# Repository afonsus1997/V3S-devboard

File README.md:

# V3S-devboard

## Hardware

Using V3S lib from https://github.com/balmerdx/AllwinnerV3S_KiCad

## Software

Build environment based on Funkey project

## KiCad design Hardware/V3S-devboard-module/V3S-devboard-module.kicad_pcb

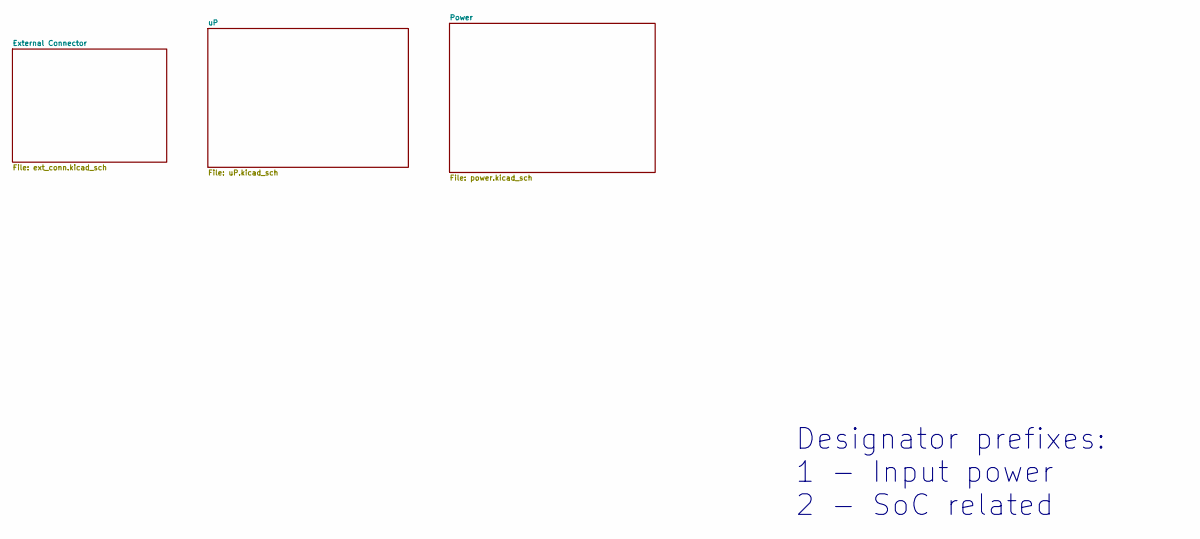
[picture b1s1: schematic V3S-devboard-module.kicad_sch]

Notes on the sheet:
Designator prefixes: 1 - Input power 2 - SoC related

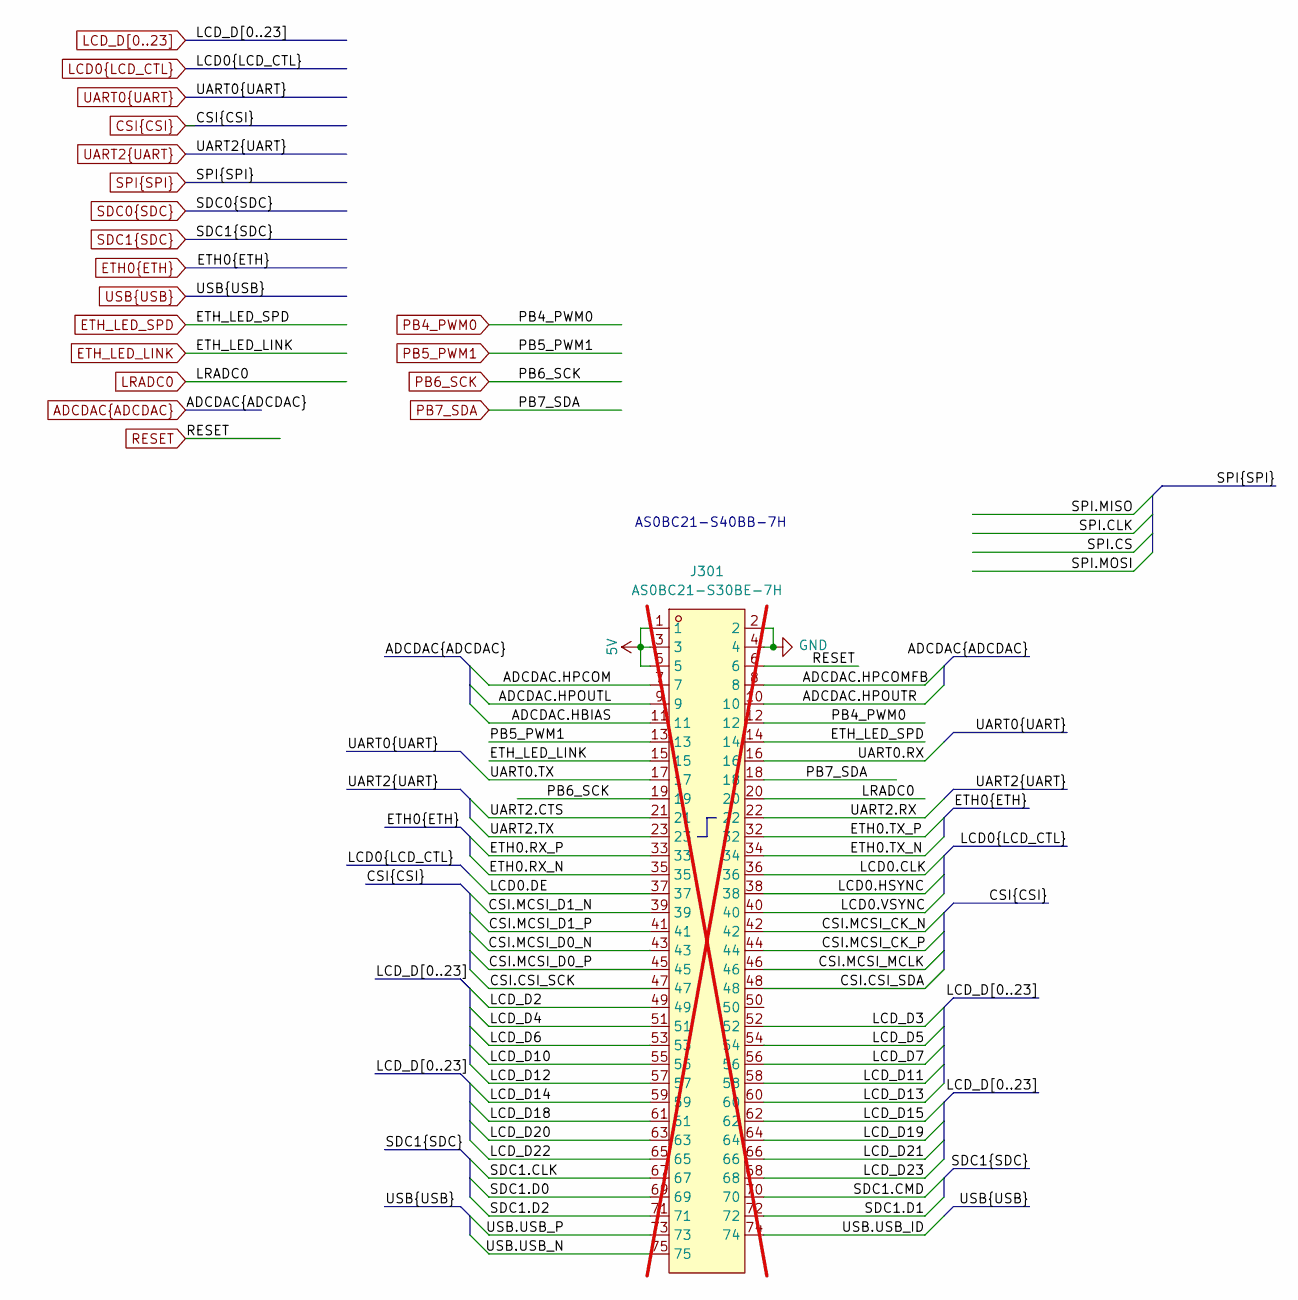
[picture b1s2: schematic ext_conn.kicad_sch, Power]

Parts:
J301: AS0BC21-S30BE-7H; m2-padKeyE; LCSC Part C3020019; not fitted

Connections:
5V: J301.1, J301.3, J301.5; also elsewhere on the board
ADCDAC.HBIAS: J301.11; also elsewhere on the board
ADCDAC.HPCOM: J301.7; also elsewhere on the board
ADCDAC.HPCOMFB: J301.8; also elsewhere on the board
ADCDAC.HPOUTL: J301.9; also elsewhere on the board
ADCDAC.HPOUTR: J301.10; also elsewhere on the board
CSI.CSI_SCK: J301.47; also elsewhere on the board
CSI.CSI_SDA: J301.48; also elsewhere on the board
CSI.MCSI_CK_N: J301.42; also elsewhere on the board
CSI.MCSI_CK_P: J301.44; also elsewhere on the board
CSI.MCSI_D0_N: J301.43; also elsewhere on the board
CSI.MCSI_D0_P: J301.45; also elsewhere on the board
CSI.MCSI_D1_N: J301.39; also elsewhere on the board
CSI.MCSI_D1_P: J301.41; also elsewhere on the board
CSI.MCSI_MCLK: J301.46; also elsewhere on the board
ETH0.RX_N: J301.35; also elsewhere on the board
ETH0.RX_P: J301.33; also elsewhere on the board
ETH0.TX_N: J301.34; also elsewhere on the board
ETH0.TX_P: J301.32; also elsewhere on the board
ETH_LED_LINK: J301.15; also elsewhere on the board
ETH_LED_SPD: J301.14; also elsewhere on the board
GND: J301.2, J301.4; also elsewhere on the board
LCD0.CLK: J301.36; also elsewhere on the board
LCD0.DE: J301.37; also elsewhere on the board
LCD0.HSYNC: J301.38; also elsewhere on the board
LCD0.VSYNC: J301.40; also elsewhere on the board
LCD_D2: J301.49; also elsewhere on the board
LCD_D3: J301.52; also elsewhere on the board
LCD_D4: J301.51; also elsewhere on the board
LCD_D5: J301.54; also elsewhere on the board
LCD_D6: J301.53; also elsewhere on the board
LCD_D7: J301.56; also elsewhere on the board
LCD_D10: J301.55; also elsewhere on the board
LCD_D11: J301.58; also elsewhere on the board
LCD_D12: J301.57; also elsewhere on the board
LCD_D13: J301.60; also elsewhere on the board
LCD_D14: J301.59; also elsewhere on the board
LCD_D15: J301.62; also elsewhere on the board
LCD_D18: J301.61; also elsewhere on the board
LCD_D19: J301.64; also elsewhere on the board
LCD_D20: J301.63; also elsewhere on the board
LCD_D21: J301.66; also elsewhere on the board
LCD_D22: J301.65; also elsewhere on the board
LCD_D23: J301.68; also elsewhere on the board
LRADC0: J301.20; also elsewhere on the board
PB4_PWM0: J301.12; also elsewhere on the board
PB5_PWM1: J301.13; also elsewhere on the board
PB6_SCK: J301.19; also elsewhere on the board
PB7_SDA: J301.18; also elsewhere on the board
RESET: J301.6; also elsewhere on the board
SDC1.CLK: J301.67; also elsewhere on the board
SDC1.CMD: J301.70; also elsewhere on the board
SDC1.D0: J301.69; also elsewhere on the board
SDC1.D1: J301.72; also elsewhere on the board
SDC1.D2: J301.71; also elsewhere on the board
UART0.RX: J301.16; also elsewhere on the board
UART0.TX: J301.17; also elsewhere on the board
UART2.CTS: J301.21; also elsewhere on the board
UART2.RX: J301.22; also elsewhere on the board
UART2.TX: J301.23; also elsewhere on the board
USB.USB_ID: J301.74; also elsewhere on the board
USB.USB_N: J301.75; also elsewhere on the board
USB.USB_P: J301.73; also elsewhere on the board

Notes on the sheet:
AS0BC21-S40BB-7H

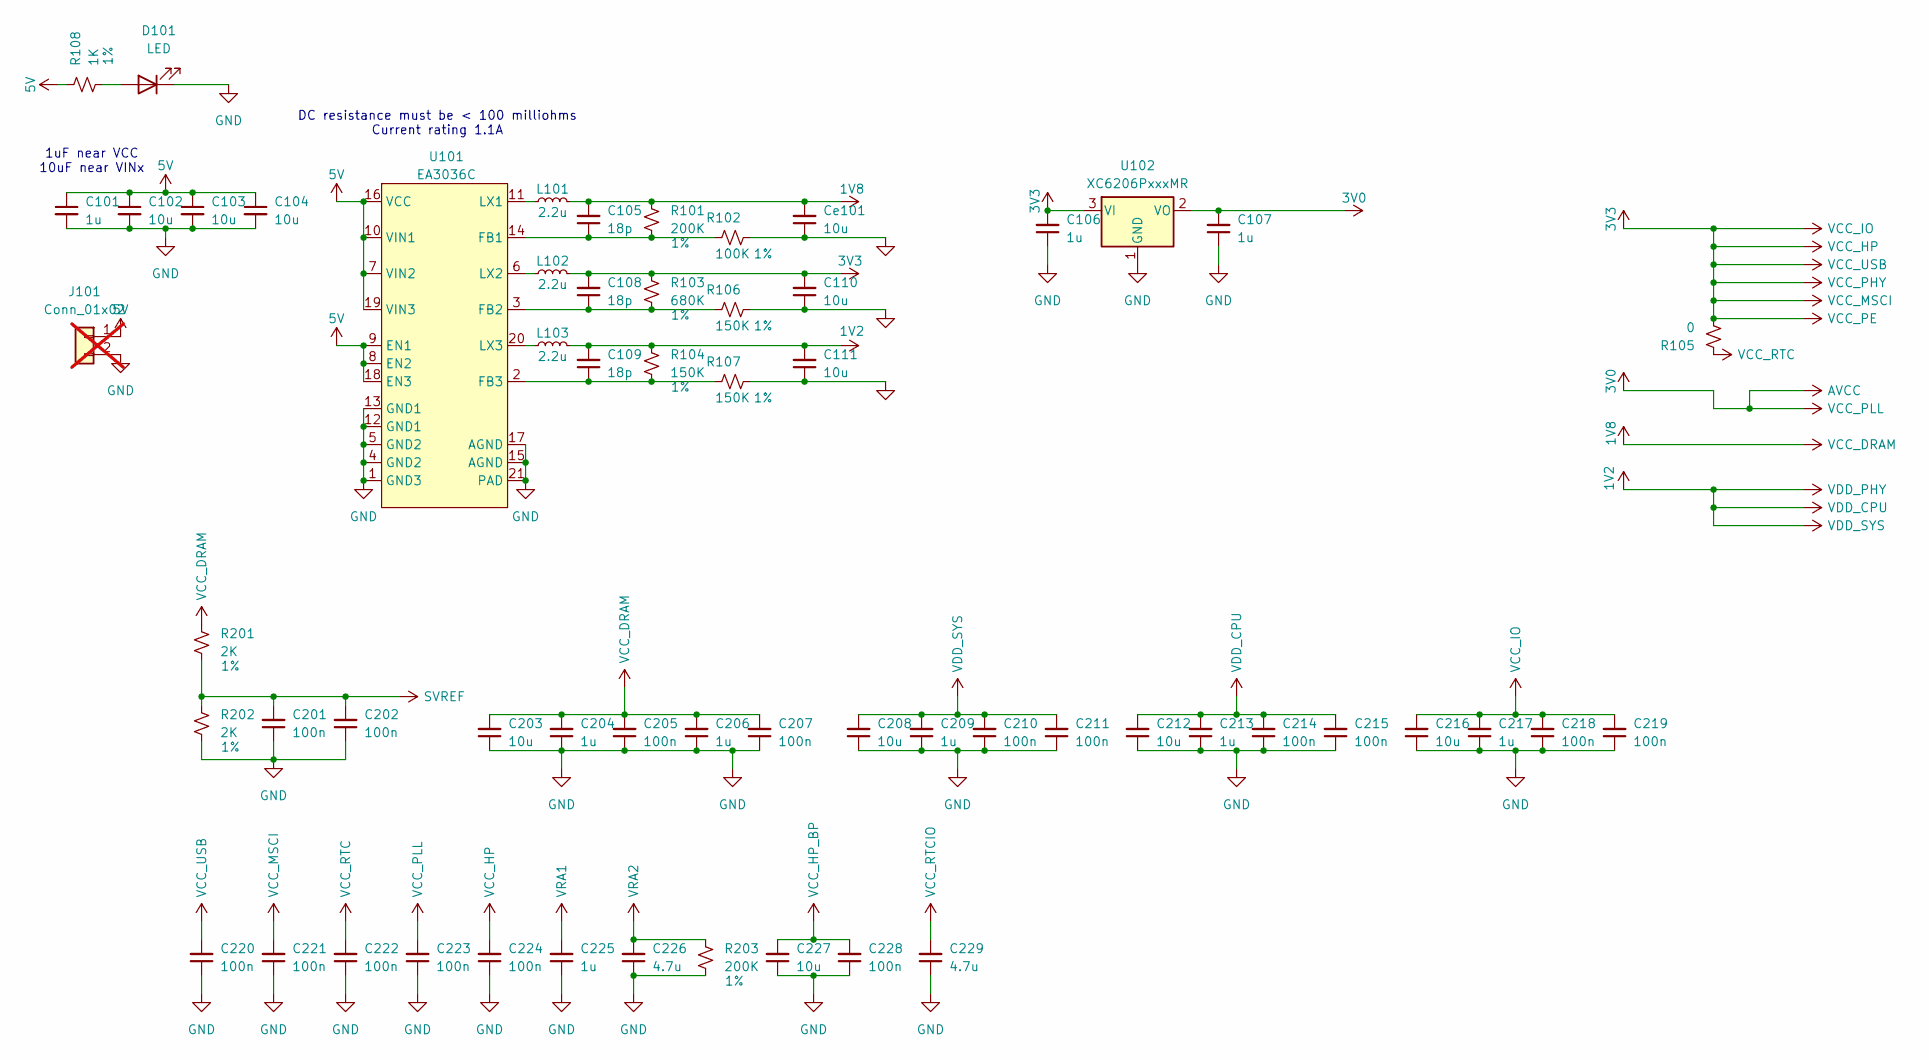
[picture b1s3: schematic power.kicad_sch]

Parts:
C101, C106, C107, C204, C206, C209, C213, C217, C225: 1u; C_0603_1608Metric; LCSC C5673
C102, C103, C104, C110, C111, C203, C208, C212, C216, C227: 10u; C_0603_1608Metric; LCSC C1691
C105, C108, C109: 18p; C_0402_1005Metric; LCSC C541431
C201, C202, C205, C207, C210, C211, C214, C215, C218, C219, C220, C221, C222, C223, C224, C228: 100n; C_0402_1005Metric; LCSC C1525
C226, C229: 4.7u; C_0603_1608Metric; LCSC C1705
Ce101: 10u; C_0603_1608Metric; LCSC C1691
D101: LED; LED_0603_1608Metric
J101: Conn_01x02; PinHeader_1x02_P2.54mm_Vertical; not fitted
L101, L102, L103: 2.2u; L_1008_2520Metric; LCSC C86092
R101, R203: 200K; R_0402_1005Metric; LCSC C114763
R102: 100K; R_0402_1005Metric; LCSC C60491
R103: 680K; R_0402_1005Metric; LCSC C163456
R104, R106, R107: 150K; R_0402_1005Metric; LCSC C93947
R105: 0; R_0402_1005Metric; LCSC C106231
R108: 1K; R_0402_1005Metric; LCSC C114763
R201, R202: 2K; R_0402_1005Metric; LCSC C60488
U101: EA3036C; WQFN-20-1EP_3x3mm_P0.4mm_EP1.7x1.7mm; LCSC C570857
U102: XC6206PxxxMR; SOT-23-3; LCSC C5148691

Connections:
1V2: C109.2, C111.2, C208.2, C209.2, C210.2, C211.2, C212.2, C213.2, C214.2, C215.2, L103.2, R104.1; also elsewhere on the board
1V8: C105.2, C203.2, C204.2, C205.2, C206.2, C207.2, Ce101.2, L101.2, R101.1, R201.1; also elsewhere on the board
3V0: C107.2, C223.2, U102.2 (VO); also elsewhere on the board
3V3: C106.2, C108.2, C110.2, C216.2, C217.2, C218.2, C219.2, C220.2, C221.2, C224.2, L102.2, R103.1, R105.2, U102.3 (VI); also elsewhere on the board
5V: C101.1, C102.1, C103.1, C104.1, J101.1, R108.1, U101.7 (VIN2), U101.8 (EN2), U101.9 (EN1), U101.10 (VIN1), U101.16 (VCC), U101.18 (EN3), U101.19 (VIN3); also elsewhere on the board
GND: C101.2, C102.2, C103.2, C104.2, C106.1, C107.1, C110.1, C111.1, C201.1, C202.1, C203.1, C204.1, C205.1, C206.1, C207.1, C208.1, C209.1, C210.1, C211.1, C212.1, C213.1, C214.1, C215.1, C216.1, C217.1, C218.1, C219.1, C220.1, C221.1, C222.1, C223.1, C224.1, C225.1, C226.1, C227.1, C228.1, C229.1, Ce101.1, D101.1 (K), J101.2, R102.2, R106.2, R107.2, R202.2, R203.2, U101.1 (GND3), U101.4 (GND2), U101.5 (GND2), U101.12 (GND1), U101.13 (GND1), U101.15 (AGND), U101.17 (AGND), U101.21 (PAD), U102.1 (GND); also elsewhere on the board
unnamed: D101.2 (A), R108.2
unnamed: C105.1, R101.2, R102.1, U101.14 (FB1)
unnamed: C108.1, R103.2, R106.1, U101.3 (FB2)
unnamed: C109.1, R104.2, R107.1, U101.2 (FB3)
unnamed: L101.1, U101.11 (LX1)
unnamed: L102.1, U101.6 (LX2)
unnamed: L103.1, U101.20 (LX3)
SVREF: C201.2, C202.2, R201.2, R202.1; also elsewhere on the board
VCC_HP_BP: C227.2, C228.2; also elsewhere on the board
VCC_RTC: C222.2, R105.1; also elsewhere on the board
VCC_RTCIO: C229.2; also elsewhere on the board
VRA1: C225.2; also elsewhere on the board
VRA2: C226.2, R203.1; also elsewhere on the board

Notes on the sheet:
DC resistance must be < 100 milliohms Current rating 1.1A
1uF near VCC 10uF near VINx

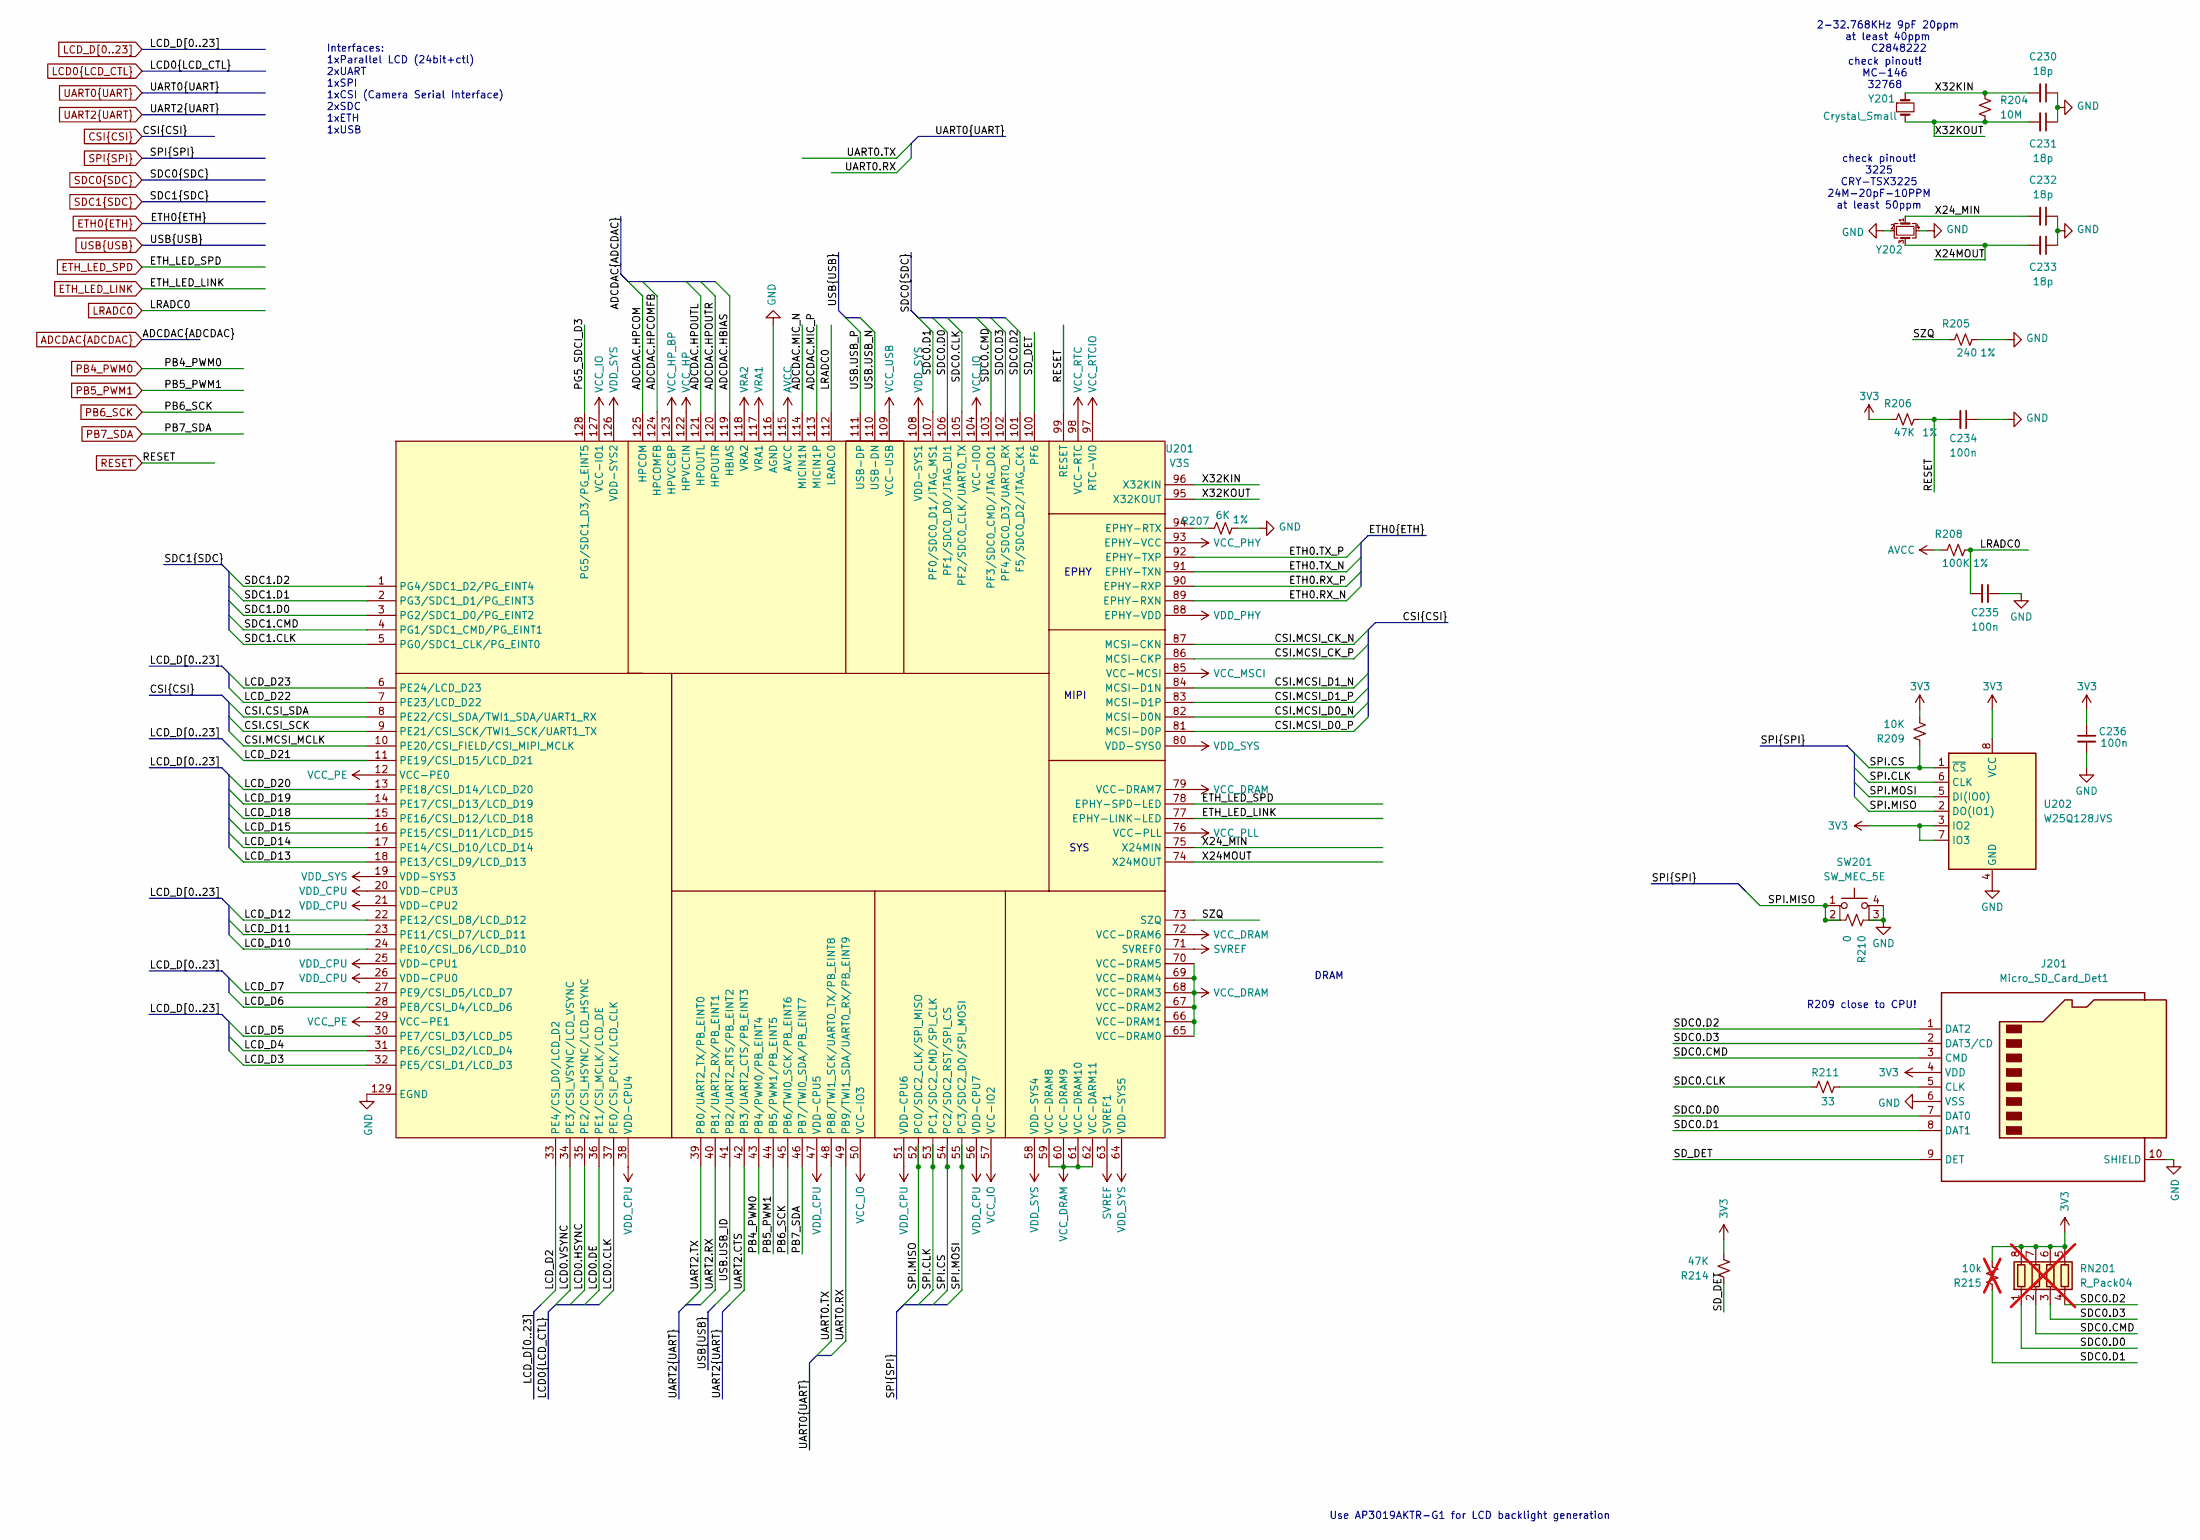
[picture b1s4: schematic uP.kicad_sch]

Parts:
C230, C231, C232, C233: 18p; C_0402_1005Metric; LCSC C541431
C234, C235, C236: 100n; C_0402_1005Metric; LCSC C1525
J201: Micro_SD_Card_Det1; J_sd_micro_socket; LCSC C7529389
R204: 10M; R_0402_1005Metric; LCSC C138067
R205: 240; R_0402_1005Metric; LCSC C114755
R206, R214: 47K; R_0402_1005Metric; LCSC C93943
R207: 6K; R_0805_2012Metric; LCSC C2828725
R208: 100K; R_0402_1005Metric; LCSC C60491
R209: 10K; R_0402_1005Metric; LCSC C60490
R210: 0; R_0402_1005Metric; LCSC C106231
R211: 33; R_0402_1005Metric; LCSC C138002
R215: 10k; R_0402_1005Metric; LCSC C60490; not fitted
RN201: R_Pack04; R_Array_Concave_4x0402; LCSC C1736647; not fitted
SW201: SW_MEC_5E; SW_SKRPACE010; LCSC C139797
U201: V3S; LQFP-128_L14.0-W14.0-P0.40-LS16.0-BL-EP5.0; LCSC C2687449
U202: W25Q128JVS; SOIC-8_5.23x5.23mm_P1.27mm; LCSC C97521
Y201: Crystal_Small; Crystal_SMD_3215-2Pin_3.2x1.5mm; LCSC C2848222
Y202: Crystal_GND24_Small; Crystal_SMD_2520-4Pin_2.5x2.0mm; LCSC C15643

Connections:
1V2: U201.19 (VDD-SYS3), U201.20 (VDD-CPU3), U201.21 (VDD-CPU2), U201.25 (VDD-CPU1), U201.26 (VDD-CPU0), U201.38 (VDD-CPU4), U201.47 (VDD-CPU5), U201.51 (VDD-CPU6), U201.56 (VDD-CPU7), U201.58 (VDD-SYS4), U201.64 (VDD-SYS5), U201.80 (VDD-SYS0), U201.88 (EPHY-VDD), U201.108 (VDD-SYS1), U201.126 (VDD-SYS2); also elsewhere on the board
1V8: U201.59 (VCC-DRAM8), U201.60 (VCC-DRAM9), U201.61 (VCC-DRAM10), U201.62 (VCC-DARM11), U201.65 (VCC-DRAM0), U201.66 (VCC-DRAM1), U201.67 (VCC-DRAM2), U201.68 (VCC-DRAM3), U201.69 (VCC-DRAM4), U201.70 (VCC-DRAM5), U201.72 (VCC-DRAM6), U201.79 (VCC-DRAM7); also elsewhere on the board
3V0: R208.1, U201.76 (VCC-PLL), U201.115 (AVCC); also elsewhere on the board
3V3: C236.1, J201.4 (VDD), R206.1, R209.2, R214.2, R215.2, RN201.5 (R4.2), RN201.6 (R3.2), RN201.7 (R2.2), RN201.8 (R1.2), U201.12 (VCC-PE0), U201.29 (VCC-PE1), U201.50 (VCC-IO3), U201.57 (VCC-IO2), U201.85 (VCC-MCSI), U201.93 (EPHY-VCC), U201.104 (VCC-IO0), U201.109 (VCC-USB), U201.122 (HPVCCIN), U201.127 (VCC-IO1), U202.3 (IO2), U202.7 (IO3), U202.8 (VCC); also elsewhere on the board
/uP/PG5_SDCI_D3: U201.128 (PG5/SDC1_D3/PG_EINT5)
/uP/SD_DET: J201.9 (DET), R214.1, U201.100 (PF6)
/uP/SZQ: R205.1, U201.73 (SZQ)
/uP/X24MOUT: C233.2, U201.74 (X24MOUT), Y202.3
/uP/X24_MIN: C232.2, U201.75 (X24MIN), Y202.1
/uP/X32KIN: C230.2, R204.1, U201.96 (X32KIN), Y201.1
/uP/X32KOUT: C231.2, R204.2, U201.95 (X32KOUT), Y201.2
ADCDAC.HBIAS: U201.119 (HBIAS); also elsewhere on the board
ADCDAC.HPCOM: U201.125 (HPCOM); also elsewhere on the board
ADCDAC.HPCOMFB: U201.124 (HPCOMFB); also elsewhere on the board
ADCDAC.HPOUTL: U201.121 (HPOUTL); also elsewhere on the board
ADCDAC.HPOUTR: U201.120 (HPOUTR); also elsewhere on the board
ADCDAC.MIC_N: U201.114 (MICIN1N)
ADCDAC.MIC_P: U201.113 (MICIN1P)
CSI.CSI_SCK: U201.9 (PE21/CSI_SCK/TWI1_SCK/UART1_TX); also elsewhere on the board
CSI.CSI_SDA: U201.8 (PE22/CSI_SDA/TWI1_SDA/UART1_RX); also elsewhere on the board
CSI.MCSI_CK_N: U201.87 (MCSI-CKN); also elsewhere on the board
CSI.MCSI_CK_P: U201.86 (MCSI-CKP); also elsewhere on the board
CSI.MCSI_D0_N: U201.82 (MCSI-D0N); also elsewhere on the board
CSI.MCSI_D0_P: U201.81 (MCSI-D0P); also elsewhere on the board
CSI.MCSI_D1_N: U201.84 (MCSI-D1N); also elsewhere on the board
CSI.MCSI_D1_P: U201.83 (MCSI-D1P); also elsewhere on the board
CSI.MCSI_MCLK: U201.10 (PE20/CSI_FIELD/CSI_MIPI_MCLK); also elsewhere on the board
ETH0.RX_N: U201.89 (EPHY-RXN); also elsewhere on the board
ETH0.RX_P: U201.90 (EPHY-RXP); also elsewhere on the board
ETH0.TX_N: U201.91 (EPHY-TXN); also elsewhere on the board
ETH0.TX_P: U201.92 (EPHY-TXP); also elsewhere on the board
ETH_LED_LINK: U201.77 (EPHY-LINK-LED); also elsewhere on the board
ETH_LED_SPD: U201.78 (EPHY-SPD-LED); also elsewhere on the board
GND: C230.1, C231.1, C232.1, C233.1, C234.1, C235.1, C236.2, J201.6 (VSS), J201.10 (SHIELD), R205.2, R207.2, R210.1, SW201.3 (K), SW201.4 (A), U201.116 (AGND), U201.129 (EGND), U202.4 (GND), Y202.2, Y202.4; also elsewhere on the board
LCD0.CLK: U201.37 (PE0/CSI_PCLK/LCD_CLK); also elsewhere on the board
LCD0.DE: U201.36 (PE1/CSI_MCLK/LCD_DE); also elsewhere on the board
LCD0.HSYNC: U201.35 (PE2/CSI_HSYNC/LCD_HSYNC); also elsewhere on the board
LCD0.VSYNC: U201.34 (PE3/CSI_VSYNC/LCD_VSYNC); also elsewhere on the board
LCD_D2: U201.33 (PE4/CSI_D0/LCD_D2); also elsewhere on the board
LCD_D3: U201.32 (PE5/CSI_D1/LCD_D3); also elsewhere on the board
LCD_D4: U201.31 (PE6/CSI_D2/LCD_D4); also elsewhere on the board
LCD_D5: U201.30 (PE7/CSI_D3/LCD_D5); also elsewhere on the board
LCD_D6: U201.28 (PE8/CSI_D4/LCD_D6); also elsewhere on the board
LCD_D7: U201.27 (PE9/CSI_D5/LCD_D7); also elsewhere on the board
LCD_D10: U201.24 (PE10/CSI_D6/LCD_D10); also elsewhere on the board
LCD_D11: U201.23 (PE11/CSI_D7/LCD_D11); also elsewhere on the board
LCD_D12: U201.22 (PE12/CSI_D8/LCD_D12); also elsewhere on the board
LCD_D13: U201.18 (PE13/CSI_D9/LCD_D13); also elsewhere on the board
LCD_D14: U201.17 (PE14/CSI_D10/LCD_D14); also elsewhere on the board
LCD_D15: U201.16 (PE15/CSI_D11/LCD_D15); also elsewhere on the board
LCD_D18: U201.15 (PE16/CSI_D12/LCD_D18); also elsewhere on the board
LCD_D19: U201.14 (PE17/CSI_D13/LCD_D19); also elsewhere on the board
LCD_D20: U201.13 (PE18/CSI_D14/LCD_D20); also elsewhere on the board
LCD_D21: U201.11 (PE19/CSI_D15/LCD_D21); also elsewhere on the board
LCD_D22: U201.7 (PE23/LCD_D22); also elsewhere on the board
LCD_D23: U201.6 (PE24/LCD_D23); also elsewhere on the board
LRADC0: C235.2, R208.2, U201.112 (LRADC0); also elsewhere on the board
unnamed: J201.5 (CLK), R211.2
unnamed: R207.1, U201.94 (EPHY-RTX)
PB4_PWM0: U201.43 (PB4/PWM0/PB_EINT4); also elsewhere on the board
PB5_PWM1: U201.44 (PB5/PWM1/PB_EINT5); also elsewhere on the board
PB6_SCK: U201.45 (PB6/TWI0_SCK/PB_EINT6); also elsewhere on the board
PB7_SDA: U201.46 (PB7/TWI0_SDA/PB_EINT7); also elsewhere on the board
RESET: C234.2, R206.2, U201.99 (RESET); also elsewhere on the board
SDC0.CLK: R211.1, U201.105 (PF2/SDC0_CLK/UART0_TX)
SDC0.CMD: J201.3 (CMD), RN201.2 (R2.1), U201.103 (PF3/SDC0_CMD/JTAG_DO1)
SDC0.D0: J201.7 (DAT0), RN201.1 (R1.1), U201.106 (PF1/SDC0_D0/JTAG_DI1)
SDC0.D1: J201.8 (DAT1), R215.1, U201.107 (PF0/SDC0_D1/JTAG_MS1)
SDC0.D2: J201.1 (DAT2), RN201.4 (R4.1), U201.101 (F5/SDC0_D2/JTAG_CK1)
SDC0.D3: J201.2 (DAT3/CD), RN201.3 (R3.1), U201.102 (PF4/SDC0_D3/UART0_RX)
SDC1.CLK: U201.5 (PG0/SDC1_CLK/PG_EINT0); also elsewhere on the board
SDC1.CMD: U201.4 (PG1/SDC1_CMD/PG_EINT1); also elsewhere on the board
SDC1.D0: U201.3 (PG2/SDC1_D0/PG_EINT2); also elsewhere on the board
SDC1.D1: U201.2 (PG3/SDC1_D1/PG_EINT3); also elsewhere on the board
SDC1.D2: U201.1 (PG4/SDC1_D2/PG_EINT4); also elsewhere on the board
SPI.CLK: U201.53 (PC1/SDC2_CMD/SPI_CLK), U202.6 (CLK)
SPI.CS: R209.1, U201.54 (PC2/SDC2_RST/SPI_CS), U202.1 (~CS)
SPI.MISO: R210.2, SW201.1, SW201.2, U201.52 (PC0/SDC2_CLK/SPI_MISO), U202.2 (DO(IO1))
SPI.MOSI: U201.55 (PC3/SDC2_D0/SPI_MOSI), U202.5 (DI(IO0))
SVREF: U201.63 (SVREF1), U201.71 (SVREF0); also elsewhere on the board
UART0.RX: U201.49 (PB9/TWI1_SDA/UART0_RX/PB_EINT9); also elsewhere on the board
UART0.TX: U201.48 (PB8/TWI1_SCK/UART0_TX/PB_EINT8); also elsewhere on the board
UART2.CTS: U201.42 (PB3/UART2_CTS/PB_EINT3); also elsewhere on the board
UART2.RX: U201.40 (PB1/UART2_RX/PB_EINT1); also elsewhere on the board
UART2.TX: U201.39 (PB0/UART2_TX/PB_EINT0); also elsewhere on the board
USB.USB_ID: U201.41 (PB2/UART2_RTS/PB_EINT2); also elsewhere on the board
USB.USB_N: U201.110 (USB-DN); also elsewhere on the board
USB.USB_P: U201.111 (USB-DP); also elsewhere on the board
VCC_HP_BP: U201.123 (HPVCCBP); also elsewhere on the board
VCC_RTC: U201.98 (VCC-RTC); also elsewhere on the board
VCC_RTCIO: U201.97 (RTC-VIO); also elsewhere on the board
VRA1: U201.117 (VRA1); also elsewhere on the board
VRA2: U201.118 (VRA2); also elsewhere on the board

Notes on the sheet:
DRAM
check pinout! 3225 CRY-TSX3225 24M-20pF-10PPM at least 50ppm
Interfaces: 1xParallel LCD (24bit+ctl) 2xUART 1xSPI 1xCSI (Camera Serial Interface) 2xSDC 1xETH 1xUSB
EPHY
2-32.768KHz 9pF 20ppm at least 40ppm C2848222
check pinout! MC-146 32768
R209 close to CPU!
MIPI
Use AP3019AKTR-G1 for LCD backlight generation
SYS

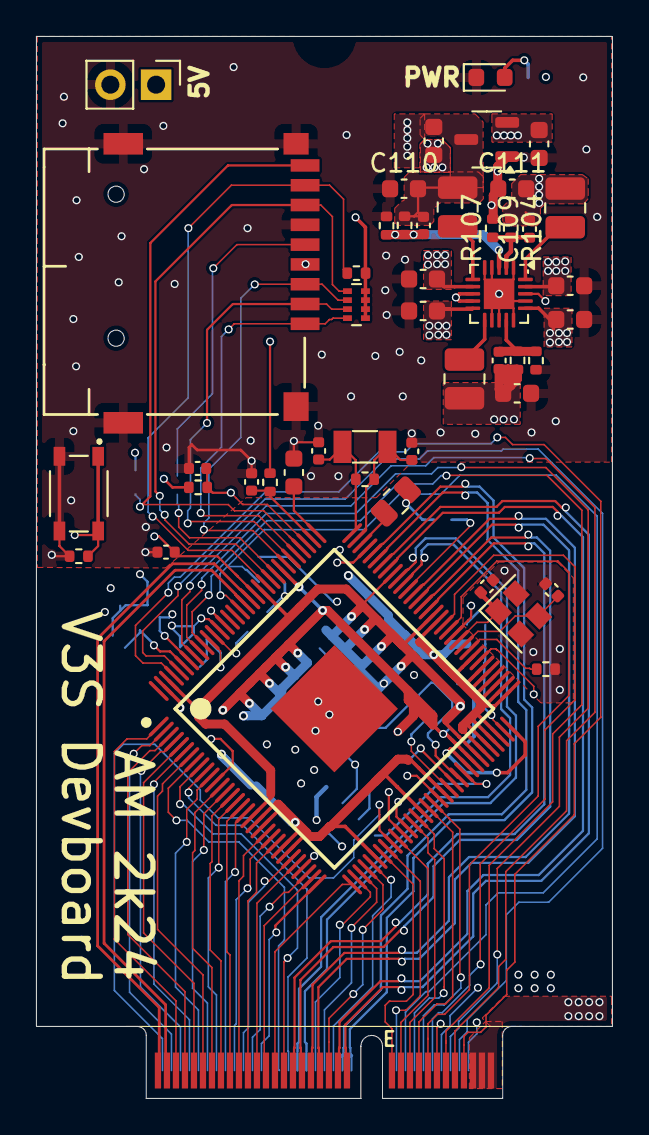
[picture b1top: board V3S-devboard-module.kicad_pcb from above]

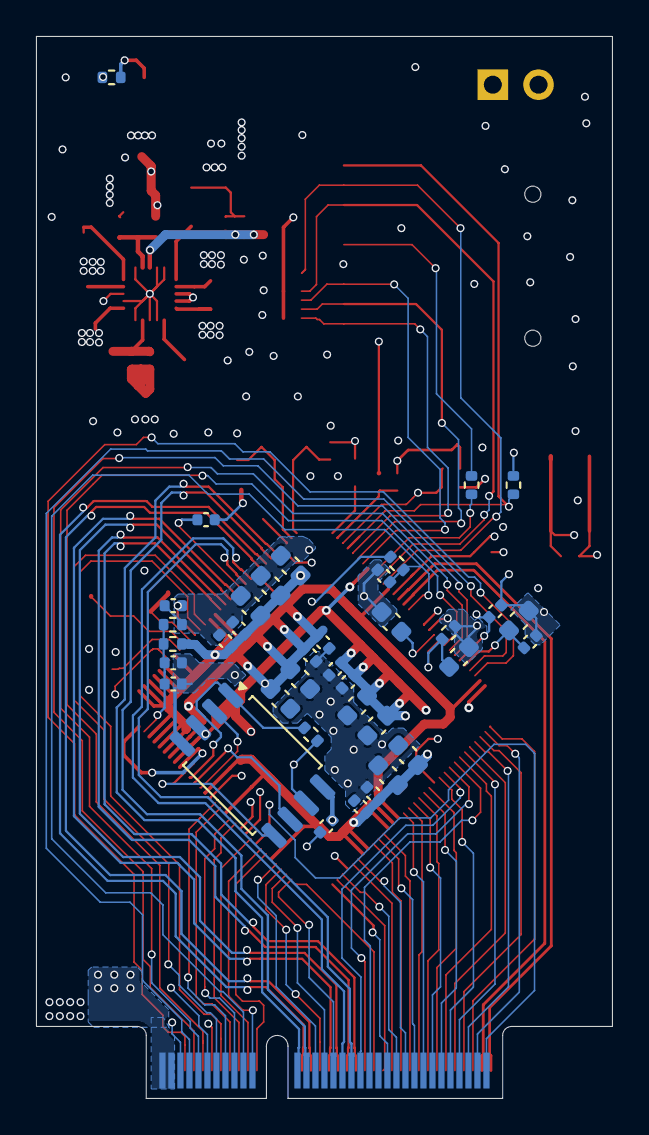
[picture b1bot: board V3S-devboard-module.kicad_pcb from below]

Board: 4 copper layers, 32.0 x 59.0 mm, 84 parts (37 on the bottom side), 98 nets.
